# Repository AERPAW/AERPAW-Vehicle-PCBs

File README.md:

# vehicle-pcbs

PCB design files for vehicles and accessories used by AERPAW project.

Designs:

- `LAM-original` contains projects (carrier, PDB) for original LAM revisions (<2025)
- `LAM-simplified` contains updated PDB (power distribution board) (>2025)
- `LightBoard` contains design for auxilary LED drivers for SAM revisions
- `SAM4-old` contains projects for original SAM revisions carrier (<2026)
- `SAME` contains projects for updated SAM revisions

Util:

- `kicad-libs` is a unified symbol/footprint library for all projects. Configure future projects to point at this!

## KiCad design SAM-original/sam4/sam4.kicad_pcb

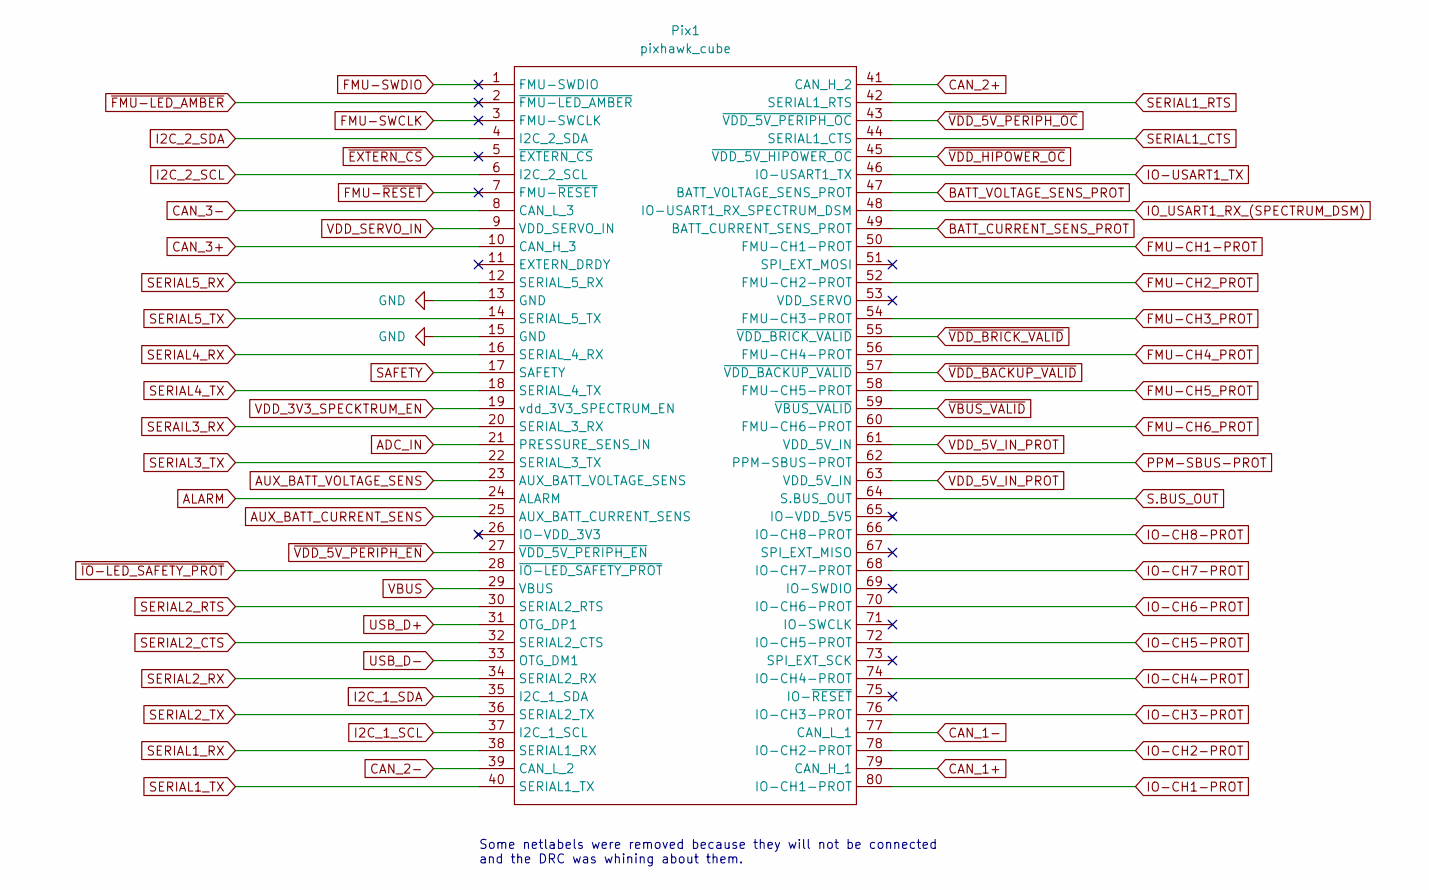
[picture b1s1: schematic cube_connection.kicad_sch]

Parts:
Pix1: pixhawk_cube; cube_footprint

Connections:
ADC_IN: Pix1.21 (PRESSURE_SENS_IN); also elsewhere on the board
ALARM: Pix1.24 (ALARM); also elsewhere on the board
AUX_BATT_CURRENT_SENS: Pix1.25 (AUX_BATT_CURRENT_SENS); also elsewhere on the board
AUX_BATT_VOLTAGE_SENS: Pix1.23 (AUX_BATT_VOLTAGE_SENS)
BATT_CURRENT_SENS_PROT: Pix1.49 (BATT_CURRENT_SENS_PROT); also elsewhere on the board
BATT_VOLTAGE_SENS_PROT: Pix1.47 (BATT_VOLTAGE_SENS_PROT); also elsewhere on the board
CAN_1+: Pix1.79 (CAN_H_1); also elsewhere on the board
CAN_1-: Pix1.77 (CAN_L_1); also elsewhere on the board
CAN_2+: Pix1.41 (CAN_H_2); also elsewhere on the board
CAN_2-: Pix1.39 (CAN_L_2); also elsewhere on the board
CAN_3+: Pix1.10 (CAN_H_3); also elsewhere on the board
CAN_3-: Pix1.8 (CAN_L_3); also elsewhere on the board
FMU-CH1-PROT: Pix1.50 (FMU-CH1-PROT); also elsewhere on the board
FMU-CH2_PROT: Pix1.52 (FMU-CH2-PROT); also elsewhere on the board
FMU-CH3_PROT: Pix1.54 (FMU-CH3-PROT); also elsewhere on the board
FMU-CH4_PROT: Pix1.56 (FMU-CH4-PROT); also elsewhere on the board
FMU-CH5_PROT: Pix1.58 (FMU-CH5-PROT); also elsewhere on the board
FMU-CH6_PROT: Pix1.60 (FMU-CH6-PROT); also elsewhere on the board
FMU-SWCLK: Pix1.3 (FMU-SWCLK)
FMU-SWDIO: Pix1.1 (FMU-SWDIO)
FMU-~RESET: Pix1.7 (FMU-~RESET)
GND: Pix1.13 (GND), Pix1.15 (GND); also elsewhere on the board
I2C_1_SCL: Pix1.37 (I2C_1_SCL)
I2C_1_SDA: Pix1.35 (I2C_1_SDA)
I2C_2_SCL: Pix1.6 (I2C_2_SCL); also elsewhere on the board
I2C_2_SDA: Pix1.4 (I2C_2_SDA); also elsewhere on the board
IO-CH1-PROT: Pix1.80 (IO-CH1-PROT); also elsewhere on the board
IO-CH2-PROT: Pix1.78 (IO-CH2-PROT); also elsewhere on the board
IO-CH3-PROT: Pix1.76 (IO-CH3-PROT); also elsewhere on the board
IO-CH4-PROT: Pix1.74 (IO-CH4-PROT); also elsewhere on the board
IO-CH5-PROT: Pix1.72 (IO-CH5-PROT); also elsewhere on the board
IO-CH6-PROT: Pix1.70 (IO-CH6-PROT); also elsewhere on the board
IO-CH7-PROT: Pix1.68 (IO-CH7-PROT); also elsewhere on the board
IO-CH8-PROT: Pix1.66 (IO-CH8-PROT); also elsewhere on the board
IO-USART1_TX: Pix1.46 (IO-USART1_TX)
IO_USART1_RX_(SPECTRUM_DSM): Pix1.48 (IO-USART1_RX_SPECTRUM_DSM)
PPM-SBUS-PROT: Pix1.62 (PPM-SBUS-PROT); also elsewhere on the board
S.BUS_OUT: Pix1.64 (S.BUS_OUT); also elsewhere on the board
SAFETY: Pix1.17 (SAFETY)
SERAIL3_RX: Pix1.20 (SERIAL_3_RX)
SERIAL1_CTS: Pix1.44 (SERIAL1_CTS); also elsewhere on the board
SERIAL1_RTS: Pix1.42 (SERIAL1_RTS); also elsewhere on the board
SERIAL1_RX: Pix1.38 (SERIAL1_RX); also elsewhere on the board
SERIAL1_TX: Pix1.40 (SERIAL1_TX); also elsewhere on the board
SERIAL2_CTS: Pix1.32 (SERIAL2_CTS); also elsewhere on the board
SERIAL2_RTS: Pix1.30 (SERIAL2_RTS); also elsewhere on the board
SERIAL2_RX: Pix1.34 (SERIAL2_RX); also elsewhere on the board
SERIAL2_TX: Pix1.36 (SERIAL2_TX); also elsewhere on the board
SERIAL3_TX: Pix1.22 (SERIAL_3_TX)
SERIAL4_RX: Pix1.16 (SERIAL_4_RX)
SERIAL4_TX: Pix1.18 (SERIAL_4_TX)
SERIAL5_RX: Pix1.12 (SERIAL_5_RX); also elsewhere on the board
SERIAL5_TX: Pix1.14 (SERIAL_5_TX)
USB_D+: Pix1.31 (OTG_DP1); also elsewhere on the board
USB_D-: Pix1.33 (OTG_DM1); also elsewhere on the board
VBUS: Pix1.29 (VBUS); also elsewhere on the board
VDD_3V3_SPECKTRUM_EN: Pix1.19 (vdd_3V3_SPECTRUM_EN); also elsewhere on the board
VDD_5V_IN_PROT: Pix1.61 (VDD_5V_IN), Pix1.63 (VDD_5V_IN); also elsewhere on the board
VDD_SERVO_IN: Pix1.9 (VDD_SERVO_IN); also elsewhere on the board
~EXTERN_CS: Pix1.5 (~EXTERN_CS)
~FMU-LED_AMBER: Pix1.2 (~FMU-LED_AMBER)
~IO-LED_SAFETY_PROT: Pix1.28 (~IO-LED_SAFETY_PROT)
~VBUS_VALID: Pix1.59 (~VBUS_VALID); also elsewhere on the board
~VDD_5V_PERIPH_EN: Pix1.27 (~VDD_5V_PERIPH_EN); also elsewhere on the board
~VDD_5V_PERIPH_OC: Pix1.43 (~VDD_5V_PERIPH_OC); also elsewhere on the board
~VDD_BACKUP_VALID: Pix1.57 (~VDD_BACKUP_VALID); also elsewhere on the board
~VDD_BRICK_VALID: Pix1.55 (~VDD_BRICK_VALID); also elsewhere on the board
~VDD_HIPOWER_OC: Pix1.45 (~VDD_5V_HIPOWER_OC); also elsewhere on the board

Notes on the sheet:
Some netlabels were removed because they will not be connected and the DRC was whining about them.

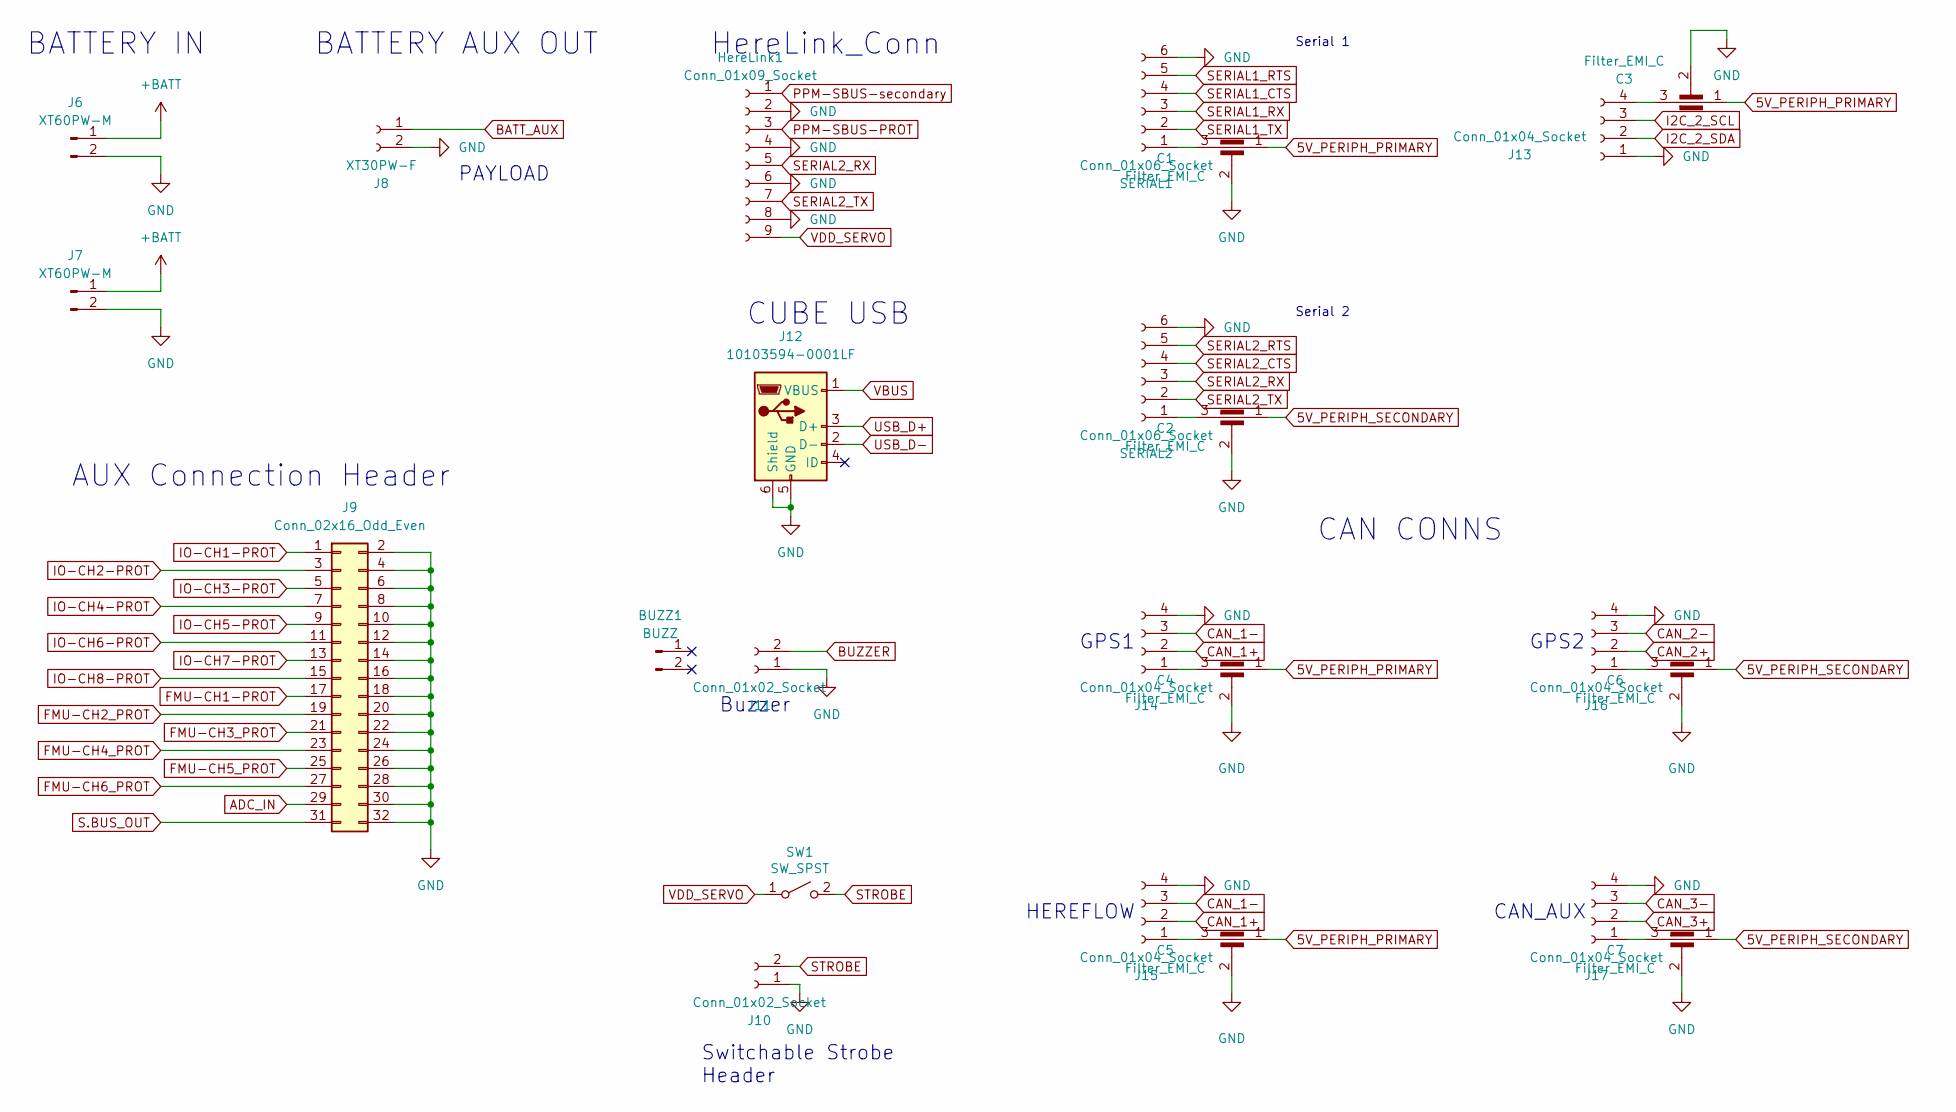
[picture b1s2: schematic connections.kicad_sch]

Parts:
BUZZ1: BUZZ; sam_buzzer
C1, C2, C3, C4, C5, C6, C7: Filter_EMI_C; FIL_NFM21HC224R1A3D
HereLink1: Conn_01x09_Socket; JST_GH_SM09B-GHS-TB_1x09-1MP_P1.25mm_Horizontal
J6, J7: XT60PW-M; AMASS_XT60PW-M_1x02_P7.20mm_Horizontal
J8: XT30PW-F; AMASS_XT30PW-F_1x02_P2.50mm_Horizontal
J9: Conn_02x16_Odd_Even; PinHeader_2x16_P2.54mm_Vertical
J10: Conn_01x02_Socket; Molex_CLIK-Mate_502386-0270_1x02-1MP_P1.25mm_Horizontal
J11: Conn_01x02_Socket; sam_buzzer_conn
J12: 10103594-0001LF; USB_Micro-B_Amphenol_10103594-0001LF_Horizontal
J13, J14, J15, J16, J17: Conn_01x04_Socket; JST_GH_BM04B-GHS-TBT_1x04-1MP_P1.25mm_Vertical
SERIAL1, SERIAL2: Conn_01x06_Socket; JST_GH_BM06B-GHS-TBT_1x06-1MP_P1.25mm_Vertical
SW1: SW_SPST; sam_slide_switch_5x5

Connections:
5V_PERIPH_PRIMARY: C1.1, C3.1, C4.1, C5.1; also elsewhere on the board
5V_PERIPH_SECONDARY: C2.1, C6.1, C7.1; also elsewhere on the board
+BATT: J6.1, J7.1; also elsewhere on the board
ADC_IN: J9.29; also elsewhere on the board
BATT_AUX: J8.1; also elsewhere on the board
BUZZER: J11.2; also elsewhere on the board
CAN_1+: J14.2, J15.2; also elsewhere on the board
CAN_1-: J14.3, J15.3; also elsewhere on the board
CAN_2+: J16.2; also elsewhere on the board
CAN_2-: J16.3; also elsewhere on the board
CAN_3+: J17.2; also elsewhere on the board
CAN_3-: J17.3; also elsewhere on the board
FMU-CH1-PROT: J9.17; also elsewhere on the board
FMU-CH2_PROT: J9.19; also elsewhere on the board
FMU-CH3_PROT: J9.21; also elsewhere on the board
FMU-CH4_PROT: J9.23; also elsewhere on the board
FMU-CH5_PROT: J9.25; also elsewhere on the board
FMU-CH6_PROT: J9.27; also elsewhere on the board
GND: C1.2, C2.2, C3.2, C4.2, C5.2, C6.2, C7.2, HereLink1.2, HereLink1.4, HereLink1.6, HereLink1.8, J6.2, J7.2, J8.2, J9.2, J9.4, J9.6, J9.8, J9.10, J9.12, J9.14, J9.16, J9.18, J9.20, J9.22, J9.24, J9.26, J9.28, J9.30, J9.32, J10.1, J11.1, J12.5 (GND), J12.6 (Shield), J13.1, J14.4, J15.4, J16.4, J17.4, SERIAL1.6, SERIAL2.6; also elsewhere on the board
I2C_2_SCL: J13.3; also elsewhere on the board
I2C_2_SDA: J13.2; also elsewhere on the board
IO-CH1-PROT: J9.1; also elsewhere on the board
IO-CH2-PROT: J9.3; also elsewhere on the board
IO-CH3-PROT: J9.5; also elsewhere on the board
IO-CH4-PROT: J9.7; also elsewhere on the board
IO-CH5-PROT: J9.9; also elsewhere on the board
IO-CH6-PROT: J9.11; also elsewhere on the board
IO-CH7-PROT: J9.13; also elsewhere on the board
IO-CH8-PROT: J9.15; also elsewhere on the board
unnamed: C3.3, J13.4
unnamed: C4.3, J14.1
unnamed: C5.3, J15.1
unnamed: C6.3, J16.1
unnamed: C7.3, J17.1
unnamed: C1.3, SERIAL1.1
unnamed: C2.3, SERIAL2.1
PPM-SBUS-PROT: HereLink1.3; also elsewhere on the board
PPM-SBUS-secondary: HereLink1.1
S.BUS_OUT: J9.31; also elsewhere on the board
SERIAL1_CTS: SERIAL1.4; also elsewhere on the board
SERIAL1_RTS: SERIAL1.5; also elsewhere on the board
SERIAL1_RX: SERIAL1.3; also elsewhere on the board
SERIAL1_TX: SERIAL1.2; also elsewhere on the board
SERIAL2_CTS: SERIAL2.4; also elsewhere on the board
SERIAL2_RTS: SERIAL2.5; also elsewhere on the board
SERIAL2_RX: HereLink1.5, SERIAL2.3; also elsewhere on the board
SERIAL2_TX: HereLink1.7, SERIAL2.2; also elsewhere on the board
STROBE: J10.2, SW1.2 (B)
USB_D+: J12.3 (D+); also elsewhere on the board
USB_D-: J12.2 (D-); also elsewhere on the board
VBUS: J12.1 (VBUS); also elsewhere on the board
VDD_SERVO: HereLink1.9, SW1.1 (A); also elsewhere on the board

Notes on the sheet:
PAYLOAD
CUBE USB
Serial 1
GPS1
CAN CONNS
Switchable Strobe Header
Buzzer
GPS2
Serial 2
HereLink_Conn
CAN_AUX
HEREFLOW
BATTERY IN
AUX Connection Header
BATTERY AUX OUT

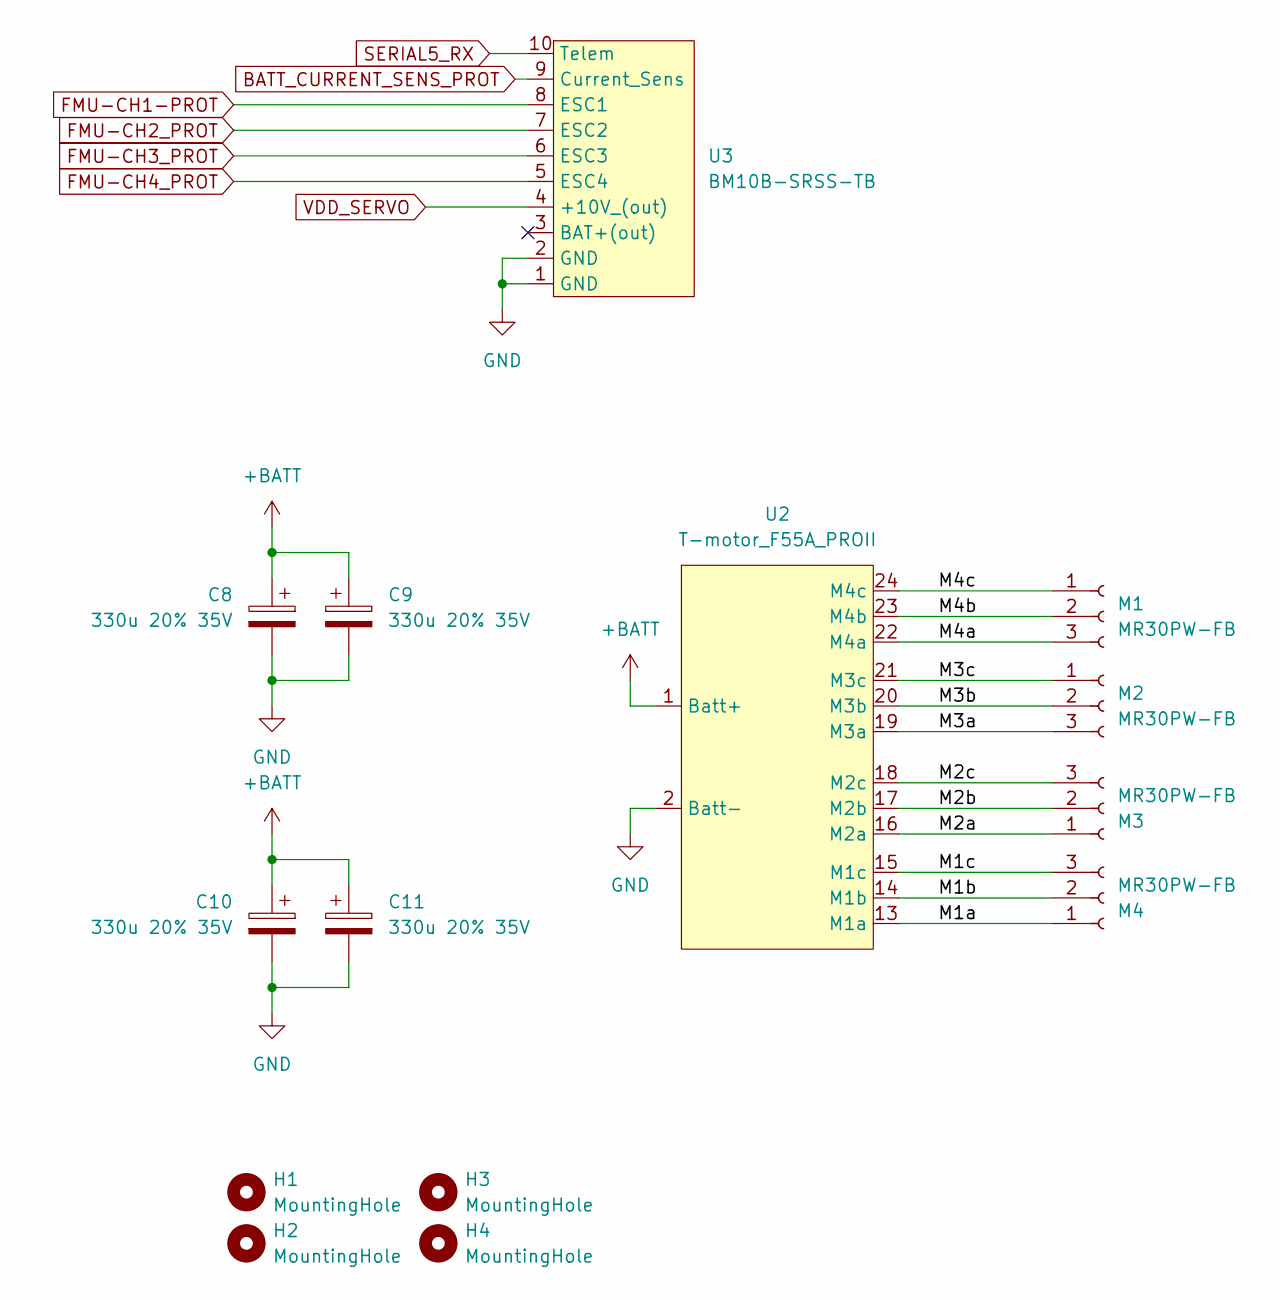
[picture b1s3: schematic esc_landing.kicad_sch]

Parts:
C8, C9, C10, C11: 330u 20% 35V; CP_Elec_10x10
H1, H2, H3, H4: MountingHole; MountingHole_3.2mm_M3_DIN965
M1, M2, M3, M4: MR30PW-FB; AMASS_MR30PW-FB_1x03_P3.50mm_Horizontal
U2: T-motor_F55A_PROII; sam_t_motor_55a_esc
U3: BM10B-SRSS-TB; JST_SH_BM10B-SRSS-TB_1x10-1MP_P1.00mm_Vertical

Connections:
+BATT: C8.1, C9.1, C10.1, C11.1, U2.1 (Batt+); also elsewhere on the board
/esc_landing/M1a: M4.1, U2.13 (M1a)
/esc_landing/M1b: M4.2, U2.14 (M1b)
/esc_landing/M1c: M4.3, U2.15 (M1c)
/esc_landing/M2a: M3.1, U2.16 (M2a)
/esc_landing/M2b: M3.2, U2.17 (M2b)
/esc_landing/M2c: M3.3, U2.18 (M2c)
/esc_landing/M3a: M2.3, U2.19 (M3a)
/esc_landing/M3b: M2.2, U2.20 (M3b)
/esc_landing/M3c: M2.1, U2.21 (M3c)
/esc_landing/M4a: M1.3, U2.22 (M4a)
/esc_landing/M4b: M1.2, U2.23 (M4b)
/esc_landing/M4c: M1.1, U2.24 (M4c)
BATT_CURRENT_SENS_PROT: U3.9 (Current_Sens); also elsewhere on the board
FMU-CH1-PROT: U3.8 (ESC1); also elsewhere on the board
FMU-CH2_PROT: U3.7 (ESC2); also elsewhere on the board
FMU-CH3_PROT: U3.6 (ESC3); also elsewhere on the board
FMU-CH4_PROT: U3.5 (ESC4); also elsewhere on the board
GND: C8.2, C9.2, C10.2, C11.2, U2.2 (Batt-), U3.1 (GND), U3.2 (GND); also elsewhere on the board
SERIAL5_RX: U3.10 (Telem); also elsewhere on the board
VDD_SERVO: U3.4 (+10V_(out)); also elsewhere on the board

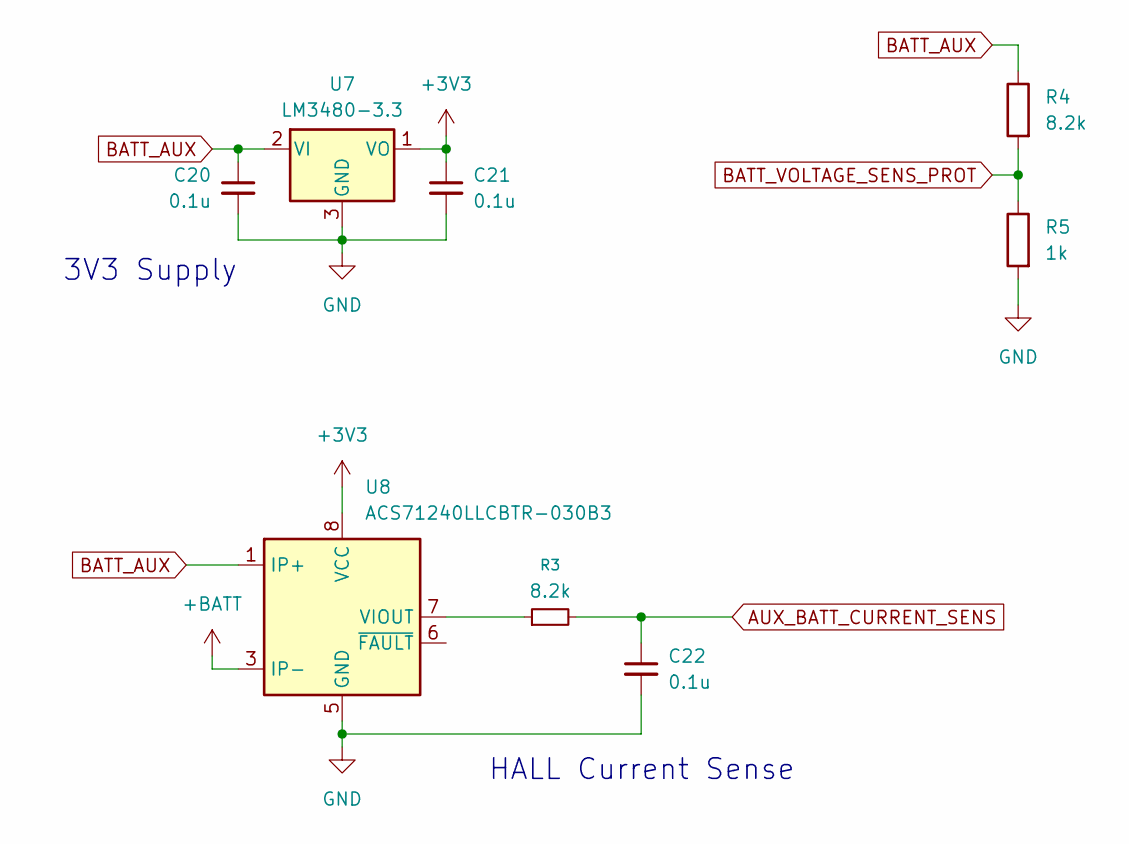
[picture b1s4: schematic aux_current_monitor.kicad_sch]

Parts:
C20, C21, C22: 0.1u; C_1206_3216Metric_Pad1.33x1.80mm_HandSolder
R3, R4: 8.2k; R_1206_3216Metric_Pad1.30x1.75mm_HandSolder
R5: 1k; R_1206_3216Metric_Pad1.30x1.75mm_HandSolder
U7: LM3480-3.3; SOT-23
U8: ACS71240LLCBTR-030B3; SOIC-8_3.9x4.9mm_P1.27mm

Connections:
+3V3: C21.1, U7.1 (VO), U8.8 (VCC)
+BATT: U8.3 (IP-), U8.4 (IP-); also elsewhere on the board
AUX_BATT_CURRENT_SENS: C22.1, R3.2; also elsewhere on the board
BATT_AUX: C20.1, R4.1, U7.2 (VI), U8.1 (IP+), U8.2 (IP+); also elsewhere on the board
BATT_VOLTAGE_SENS_PROT: R4.2, R5.1; also elsewhere on the board
GND: C20.2, C21.2, C22.2, R5.2, U7.3 (GND), U8.5 (GND); also elsewhere on the board
unnamed: R3.1, U8.7 (VIOUT)

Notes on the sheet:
HALL Current Sense
3V3 Supply

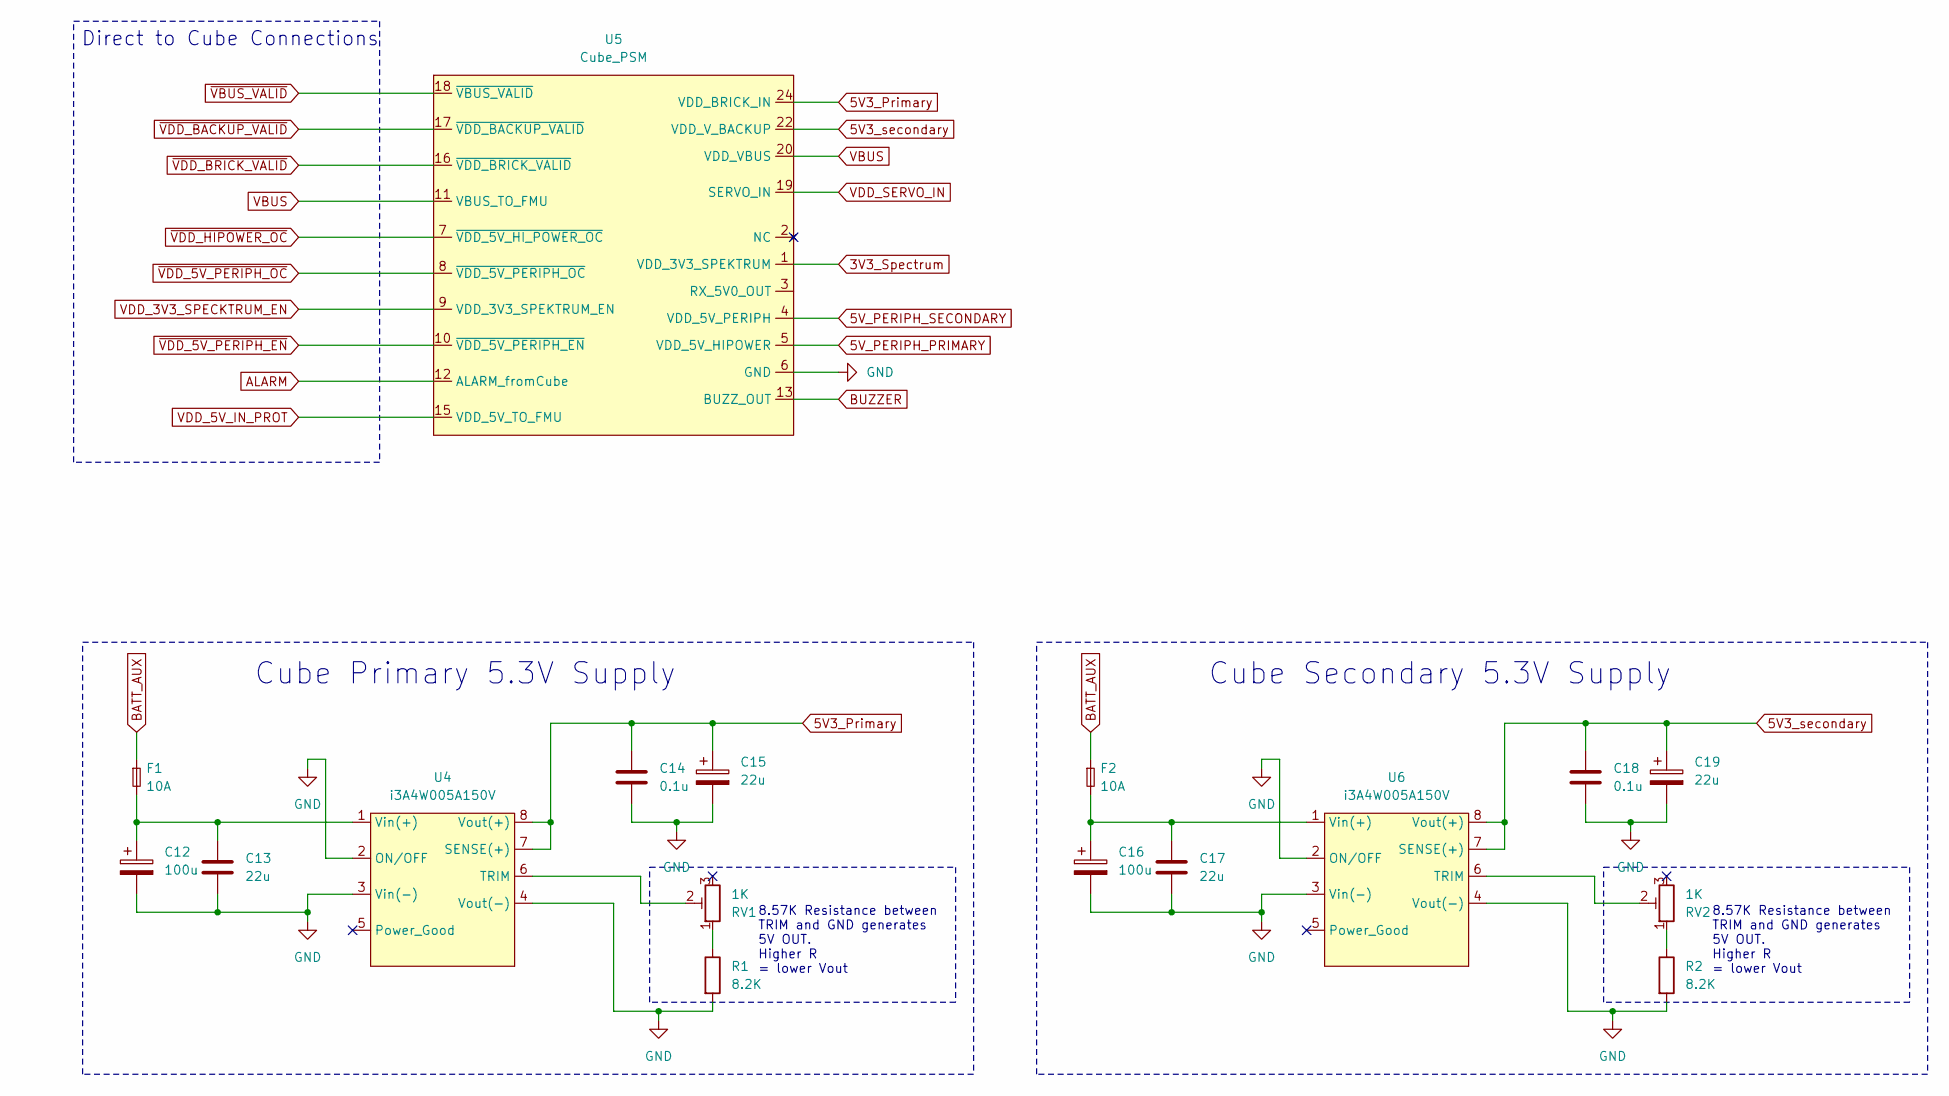
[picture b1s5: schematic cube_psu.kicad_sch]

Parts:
C12, C16: 100u; CP_Elec_10x10.5
C13, C15, C17, C19: 22u; C_1206_3216Metric
C14, C18: 0.1u; C_1206_3216Metric
F1, F2: 10A; Fuse_2512_6332Metric_Pad1.52x3.35mm_HandSolder
R1, R2: 8.2K; R_1206_3216Metric
RV1, RV2: 1K; Potentiometer_Bourns_3266W_Vertical
U4, U6: i3A4W005A150V; 1_32nd_brick_8pin
U5: Cube_PSM; cube_psm

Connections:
3V3_Spectrum: U5.1 (VDD_3V3_SPEKTRUM)
5V3_Primary: C14.1, C15.1, U4.7 (SENSE(+)), U4.8 (Vout(+)), U5.24 (VDD_BRICK_IN); also elsewhere on the board
5V3_secondary: C18.1, C19.1, U5.22 (VDD_V_BACKUP), U6.7 (SENSE(+)), U6.8 (Vout(+)); also elsewhere on the board
5V_PERIPH_PRIMARY: U5.5 (VDD_5V_HIPOWER); also elsewhere on the board
5V_PERIPH_SECONDARY: U5.4 (VDD_5V_PERIPH); also elsewhere on the board
ALARM: U5.12 (ALARM_fromCube); also elsewhere on the board
BATT_AUX: F1.1, F2.1; also elsewhere on the board
BUZZER: U5.13 (BUZZ_OUT); also elsewhere on the board
GND: C12.2, C13.2, C14.2, C15.2, C16.2, C17.2, C18.2, C19.2, R1.2, R2.2, U4.2 (ON/OFF), U4.3 (Vin(-)), U4.4 (Vout(-)), U5.6 (GND), U6.2 (ON/OFF), U6.3 (Vin(-)), U6.4 (Vout(-)); also elsewhere on the board
unnamed: R1.1, RV1.1
unnamed: R2.1, RV2.1
unnamed: RV1.2, U4.6 (TRIM)
unnamed: C12.1, C13.1, F1.2, U4.1 (Vin(+))
unnamed: RV2.2, U6.6 (TRIM)
unnamed: C16.1, C17.1, F2.2, U6.1 (Vin(+))
VBUS: U5.11 (VBUS_TO_FMU), U5.20 (VDD_VBUS); also elsewhere on the board
VDD_3V3_SPECKTRUM_EN: U5.9 (VDD_3V3_SPEKTRUM_EN); also elsewhere on the board
VDD_5V_IN_PROT: U5.15 (VDD_5V_TO_FMU); also elsewhere on the board
VDD_SERVO_IN: U5.19 (SERVO_IN); also elsewhere on the board
~VBUS_VALID: U5.18 (~VBUS_VALID); also elsewhere on the board
~VDD_5V_PERIPH_EN: U5.10 (~VDD_5V_PERIPH_EN); also elsewhere on the board
~VDD_5V_PERIPH_OC: U5.8 (~VDD_5V_PERIPH_OC); also elsewhere on the board
~VDD_BACKUP_VALID: U5.17 (~VDD_BACKUP_VALID); also elsewhere on the board
~VDD_BRICK_VALID: U5.16 (~VDD_BRICK_VALID); also elsewhere on the board
~VDD_HIPOWER_OC: U5.7 (~VDD_5V_HI_POWER_OC); also elsewhere on the board

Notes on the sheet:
8.57K Resistance between TRIM and GND generates 5V OUT. Higher R = lower Vout
Cube Secondary 5.3V Supply
Cube Primary 5.3V Supply
Direct to Cube Connections

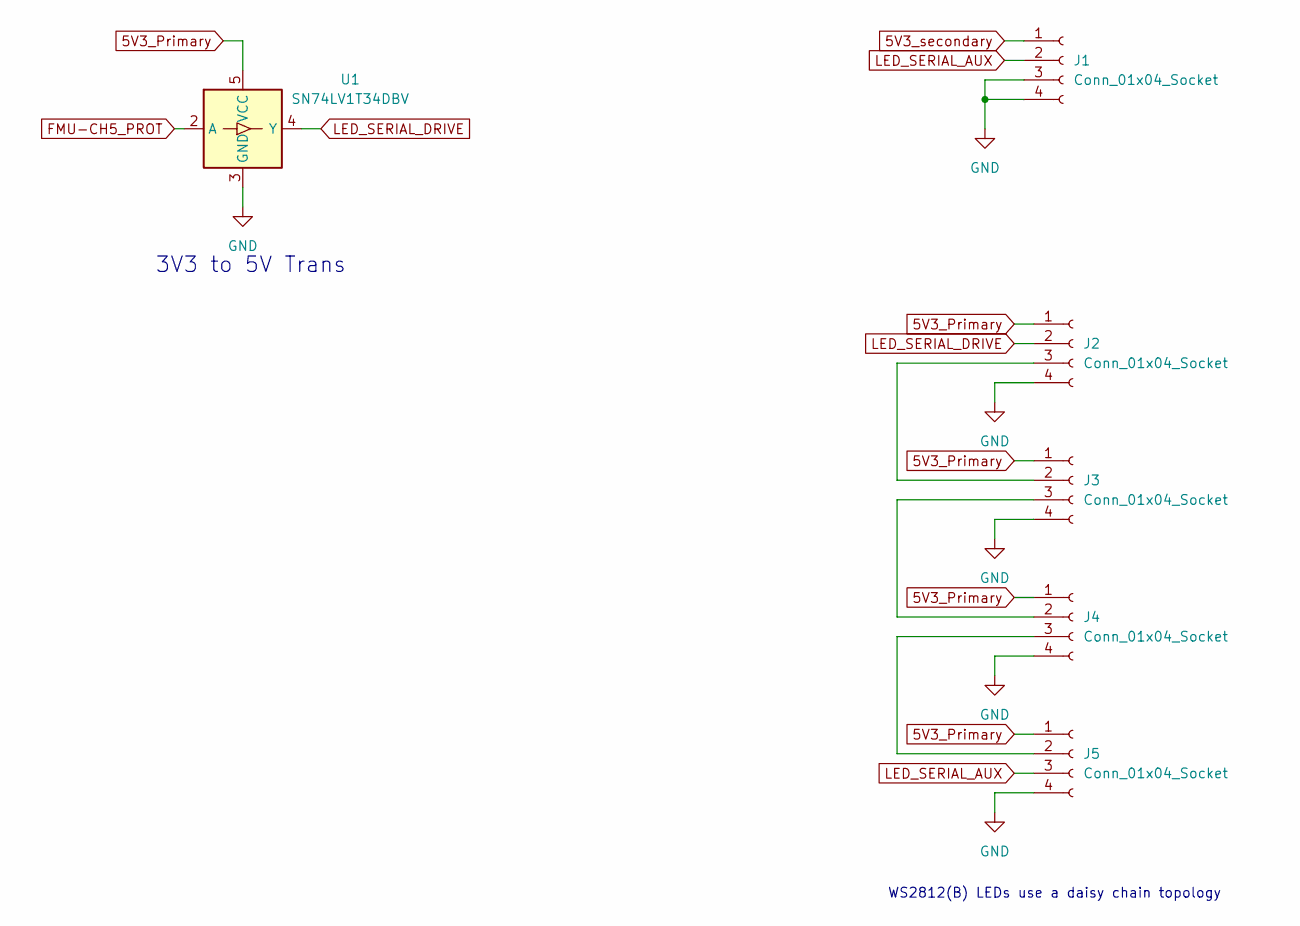
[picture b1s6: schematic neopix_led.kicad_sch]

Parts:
J1, J2, J3, J4, J5: Conn_01x04_Socket; JST_GH_BM04B-GHS-TBT_1x04-1MP_P1.25mm_Vertical
U1: SN74LV1T34DBV; SOT-23-5

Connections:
5V3_Primary: J2.1, J3.1, J4.1, J5.1, U1.5 (VCC); also elsewhere on the board
5V3_secondary: J1.1; also elsewhere on the board
FMU-CH5_PROT: U1.2 (A); also elsewhere on the board
GND: J1.3, J1.4, J2.4, J3.4, J4.4, J5.4, U1.3 (GND); also elsewhere on the board
LED_SERIAL_AUX: J1.2, J5.3
LED_SERIAL_DRIVE: J2.2, U1.4 (Y)
unnamed: J2.3, J3.2
unnamed: J3.3, J4.2
unnamed: J4.3, J5.2

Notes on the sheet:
3V3 to 5V Trans
WS2812(B) LEDs use a daisy chain topology

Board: 2 copper layers, 70 parts (12 on the bottom side), 92 nets, no tracks yet.

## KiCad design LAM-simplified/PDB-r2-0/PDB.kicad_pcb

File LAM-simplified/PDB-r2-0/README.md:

# HAM PDBs

This directory contains the KiCad (9.X) project files with design and manufacturing details for the HAM PDB (power distribution board)s.

The PDB ingests raw battery voltage and provides connectors for peripherals to hook into this net.

- 4x 2x3 2.54mm male -- to (original) carrier board
- 2x XT30 -- to aux systems
- 6x XT60 -- to motors
- 2x AS150 -- to batteries (use parallel connection)

The board also has access to a regulated 5V rail from the carrier board.
This net is currently unused, but left in for future revisions that might make use of it.

## Manufacturing

The `jlcpcb` directory and `jlcpcb.zip` contains manufacturing files that can be directly uploaded to JLCPCB's website.
A handful of settings should be changed: pick a copper weight >= 3oz, and as high of a temperature substrate as available.
The below screenshot shows an example order that should be reasonable for this application.

Assembly of this board is simple: just solder through-hole connectors into their appropriate slots.
Do not directly solder wires into this PCB.
Every connection must be made through a connector to ensure that all current expectations on wires/connectors are upheld.

When mechanically attaching this board inside the drone chassis, use brass standoffs.
The board, by design, exposes the GND net to all mechanical mounting holes.
This *should* aid with grounding the drone's chassis dependent on the rest of the mechanical design.

## BOM

A BOM can be assembled by looking at the LCSC field.
Each part number can be searched on LCSC to get ordering information and/or search terms to find similar parts.
LCSC is preferred in this case because they are the only major parts provider sourcing the needed AMASS connectors, and their system is tightly integrated with JLC.

- [2x XT30-F](https://www.lcsc.com/product-detail/C2913282.html)
- [6x XT60-F](https://www.lcsc.com/product-detail/C428722.html)
- [2x AS150UPW-M](https://www.lcsc.com/product-detail/C19268054.html)
- ?x standard 2.54mm pin headers
- [3x Keystone 5010 test points (optional)](https://www.lcsc.com/product-detail/C2906765.html)

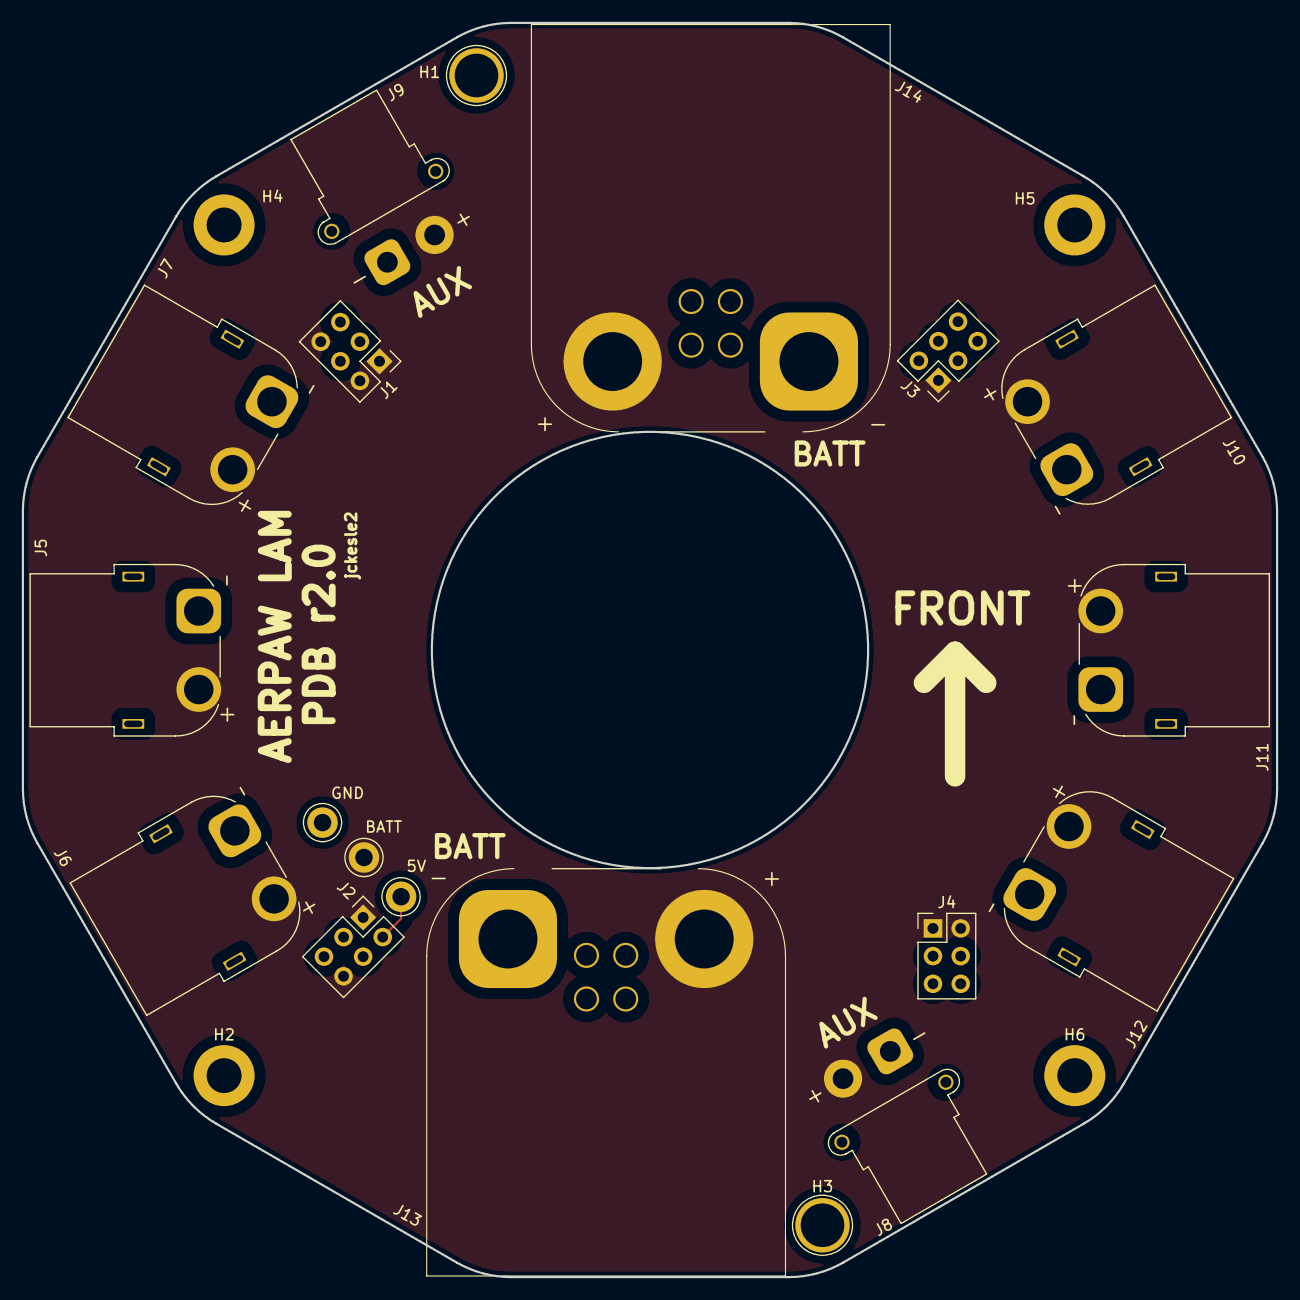
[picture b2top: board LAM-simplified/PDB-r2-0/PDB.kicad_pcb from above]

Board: 2 copper layers, 115.0 x 115.0 mm, 23 parts (0 on the bottom side), 3 nets.

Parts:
5V: TestPoint_Flag; TestPoint_Keystone_5010-5014_Multipurpose
BATT: TestPoint_Flag; TestPoint_Keystone_5010-5014_Multipurpose
GND: TestPoint_Flag; TestPoint_Keystone_5010-5014_Multipurpose
H1, H3: M4; TestPoint_Plated_Hole_D4.0mm
H2, H4, H5, H6: M3; MountingHole_3.2mm_M3_DIN965_Pad
J1, J2, J3, J4: 2.54mm 2x3; PinHeader_2x03_P2.54mm_Vertical
J5, J6, J7, J10, J11, J12: xt60-female; AMASS_XT60PW-F_1x02_P7.20mm_Horizontal
J8, J9: xt30-female; AMASS_XT30PW-F_1x02_P2.50mm_Horizontal
J13, J14: AS150UPW-M(ale); AS150UPW(2+4-)M.G.Y

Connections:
+5V: 5V.1, J2.2, J3.2
/vbat: BATT.1, J1.1, J1.2, J1.6, J2.1, J2.6, J3.1, J4.1, J4.2, J5.2, J6.2, J7.2, J8.2, J9.2, J10.2, J11.2, J12.2, J13.2, J14.2
GND: GND.1, H1.1, H2.1, H3.1, H4.1, H5.1, H6.1, J1.5, J2.5, J3.5, J3.6, J4.5, J4.6, J5.1, J6.1, J7.1, J8.1, J9.1, J10.1, J11.1, J12.1, J13.1, J14.1

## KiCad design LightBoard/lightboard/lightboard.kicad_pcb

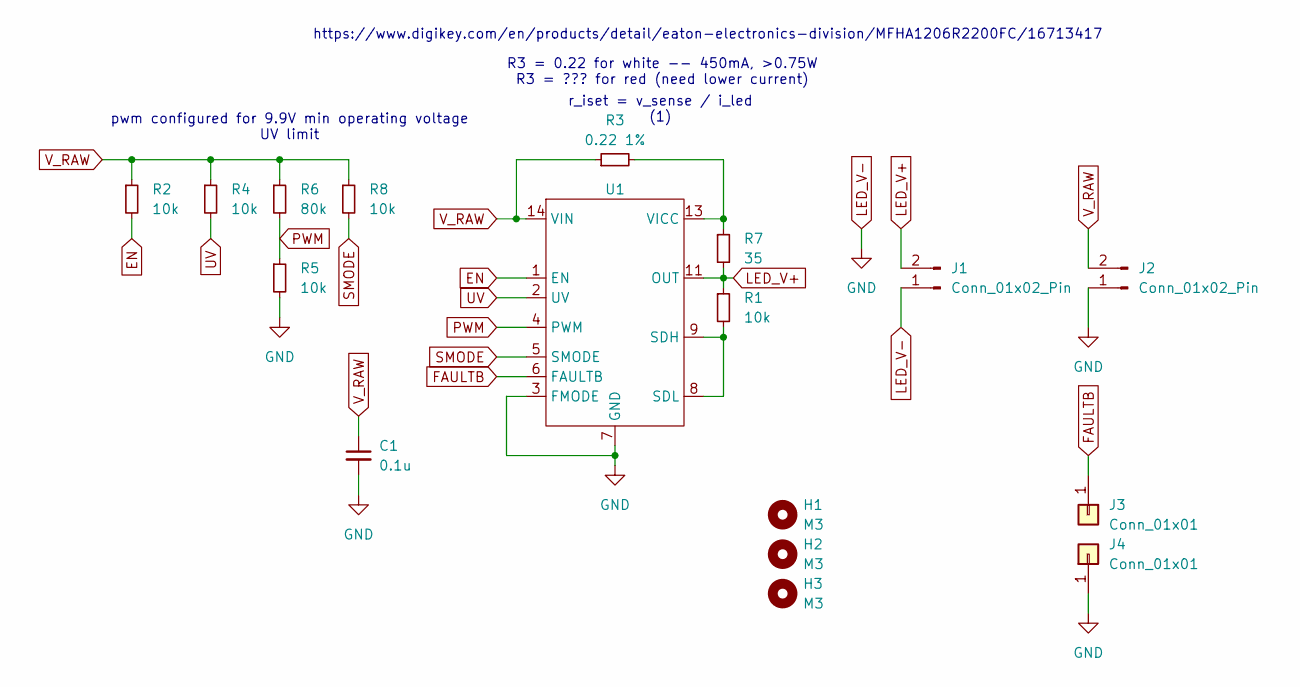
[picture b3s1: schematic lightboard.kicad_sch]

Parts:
C1: 0.1u; C_1206_3216Metric
H1, H2, H3: M3; MountingHole_3.2mm_M3
J1, J2: Conn_01x02_Pin; JST_EH_S2B-EH_1x02_P2.50mm_Horizontal
J3, J4: Conn_01x01; TestPoint_Pad_1.5x1.5mm
R1, R2, R4, R5, R8: 10k; R_1206_3216Metric
R3: 0.22 1%; R_1206_3216Metric
R6: 80k; R_1206_3216Metric
R7: 35; R_1206_3216Metric
U1: IS32LT3140A

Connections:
EN: R2.2, U1.1 (EN)
FAULTB: J3.1, U1.6 (FAULTB)
LED_V+: J1.2, R1.1, R7.2, U1.11 (OUT)
LED_V-: C1.2, J1.1, J2.1, J4.1, R5.2, U1.3 (FMODE), U1.7 (GND)
unnamed: R1.2, U1.8 (SDL), U1.9 (SDH)
unnamed: R3.2, R7.1, U1.13 (VICC)
PWM: R5.1, R6.2, U1.4 (PWM)
SMODE: R8.2, U1.5 (SMODE)
UV: R4.2, U1.2 (UV)
V_RAW: C1.1, J2.2, R2.1, R3.1, R4.1, R6.1, R8.1, U1.14 (VIN)

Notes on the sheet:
r_iset = v_sense / i_led (1)
https://www.digikey.com/en/products/detail/eaton-electronics-division/MFHA1206R2200FC/16713417
R3 = 0.22 for white -- 450mA, >0.75W R3 = ??? for red (need lower current)
pwm configured for 9.9V min operating voltage UV limit

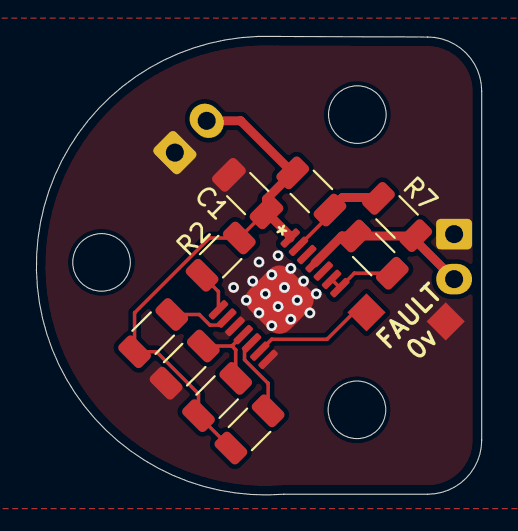
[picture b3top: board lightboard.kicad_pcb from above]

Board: 2 copper layers, 24.7 x 25.5 mm, 17 parts (1 on the bottom side), 10 nets.

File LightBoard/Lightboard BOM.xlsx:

Reference | Part | Footprint | Qty | Link | Price (1) | Price (total) | Misc
C1 | Cap 0.1u | 1206 | 1 | https://www.digikey.com/en/products/detail/vishay-sprague/29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 | 0.43 | 0.43 | Decoupling (tantalum)
J1, J2 | JST_EH 2x2.5mm Male Horiz |  | 2 | https://www.digikey.com/en/products/detail/jst-sales-america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 | 0.12 | 0.24 | Rated for 3A
R1, R2, R4, R5, R8 | Res 10k | 1206 | 5 | https://www.digikey.com/en/products/detail/yageo/RC1206FR-07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 | 0.1 | 0.5
R3 | Res 0.22 1% | 1206 | 1 | https://www.digikey.com/en/products/detail/eaton-electronics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 | 0.34 | 0.34 | Current tuning
R6 | Res 80k | 1206 | 1 | https://www.digikey.com/en/products/detail/yageo/RC1206FR-07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 | 0.1 | 0.75
R7 | Res 35 0.5W | 1206 | 1 | https://www.digikey.com/en/products/detail/yageo/SR1206JR-7T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 | 0.75 | 0.75 | Power shunt (optional)
U1 | IS32LT3140A | 14-TSSOP | 1 | https://www.digikey.com/en/products/detail/lumissil-microsys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 | 2 | 2 | LED Driver
Heat Sink |  |  | 1 | https://www.digikey.com/en/products/detail/sparkfun-electron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 | 2.44 | 2.44 | Optional
M3 Standoff |  |  | 6 | https://www.digikey.com/en/products/detail/keystone-electron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 | 0.91 | 5.46
PCB |  |  | 1 |  | 0.4 | 0.4 | JLCPCB
 |  |  |  |  |  | 13.31
